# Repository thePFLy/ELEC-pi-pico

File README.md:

# ELEC-pi-pico
Développement d'une application télémètre à ultrasons qui envoie au pico la mesure d'une distance

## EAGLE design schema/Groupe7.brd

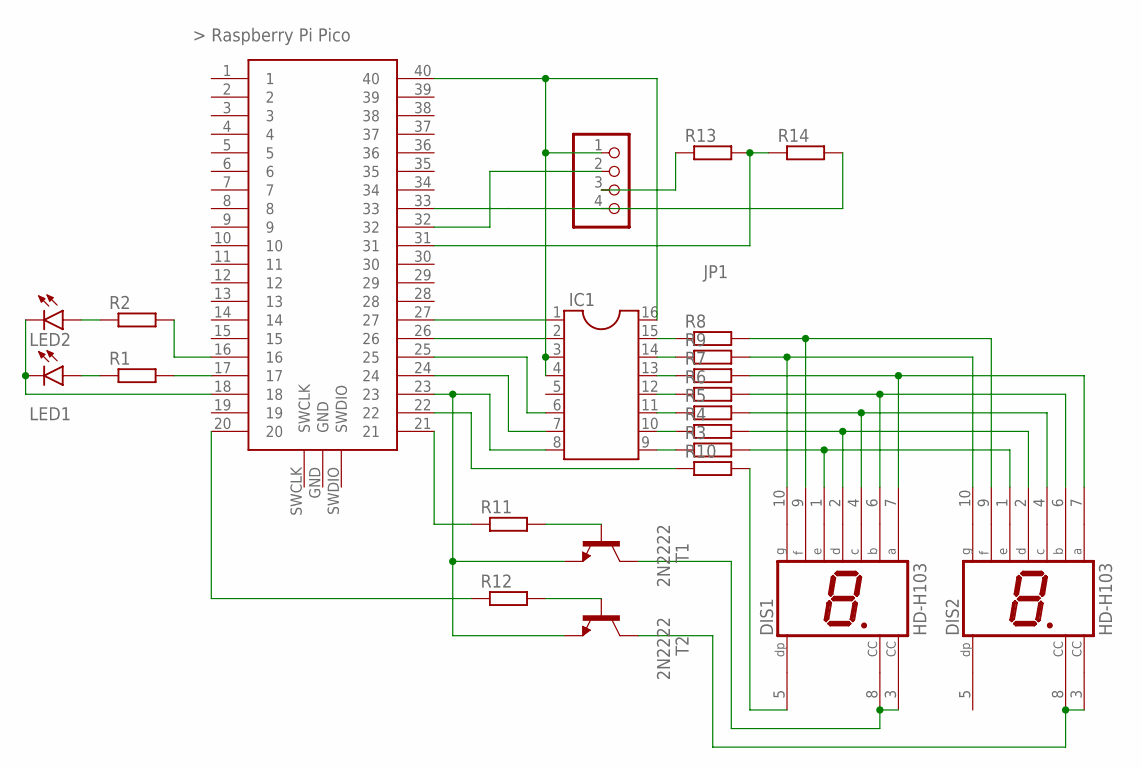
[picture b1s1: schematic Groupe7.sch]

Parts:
DIS1, DIS2: HD-H103; HDSP-M
IC1: DIL16
JP1: PINHD-1X4; 1X04
LED1, LED2: LED5MM
R1, R2, R3, R4, R5, R6, R7, R8, R9, R10, R11, R12, R13, R14: R-EU_0207/7; 0207/7
T1, T2: 2N2222; TO18
U$1: RASPBERRY-PI-PICO_TH; FT_RASPBERRY-PI-PICO_TH

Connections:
unnamed: IC1.15, R8.1
unnamed: IC1.14, R9.1
unnamed: IC1.13, R7.1
unnamed: IC1.12, R6.1
unnamed: IC1.11, R5.1
unnamed: IC1.10, R4.1
unnamed: IC1.9, R3.1
unnamed: IC1.1, U$1.27
unnamed: IC1.2, U$1.26
unnamed: IC1.6, U$1.25
unnamed: IC1.7, U$1.24
unnamed: DIS1.9 (F), DIS2.9 (F), R8.2
unnamed: DIS1.10 (G), DIS2.10 (G), R9.2
unnamed: DIS1.7 (A), DIS2.7 (A), R7.2
unnamed: DIS1.6 (B), DIS2.6 (B), R6.2
unnamed: DIS1.4 (C), DIS2.4 (C), R5.2
unnamed: DIS1.2 (D), DIS2.2 (D), R4.2
unnamed: DIS1.1 (E), DIS2.1 (E), R3.2
unnamed: IC1.3, IC1.4, IC1.16, JP1.1, U$1.40
unnamed: IC1.8, T1.1 (E), T2.1 (E), U$1.23
unnamed: JP1.2, U$1.32
unnamed: JP1.3, R13.1
unnamed: JP1.4, R14.2, U$1.33
unnamed: DIS1.3 (CC), DIS1.8 (CC), T1.3 (C)
unnamed: DIS2.3 (CC), DIS2.8 (CC), T2.3 (C)
unnamed: DIS1.5 (DP), R10.2
unnamed: R10.1, U$1.22
unnamed: R12.1, U$1.20
unnamed: R1.2, U$1.17
unnamed: R11.1, U$1.21
unnamed: R2.2, U$1.16
unnamed: LED2.A, R2.1
unnamed: LED1.A, R1.1
unnamed: LED1.K (C), LED2.K (C), U$1.18
unnamed: R11.2, T1.2 (B)
unnamed: R12.2, T2.2 (B)
unnamed: R13.2, R14.1, U$1.31

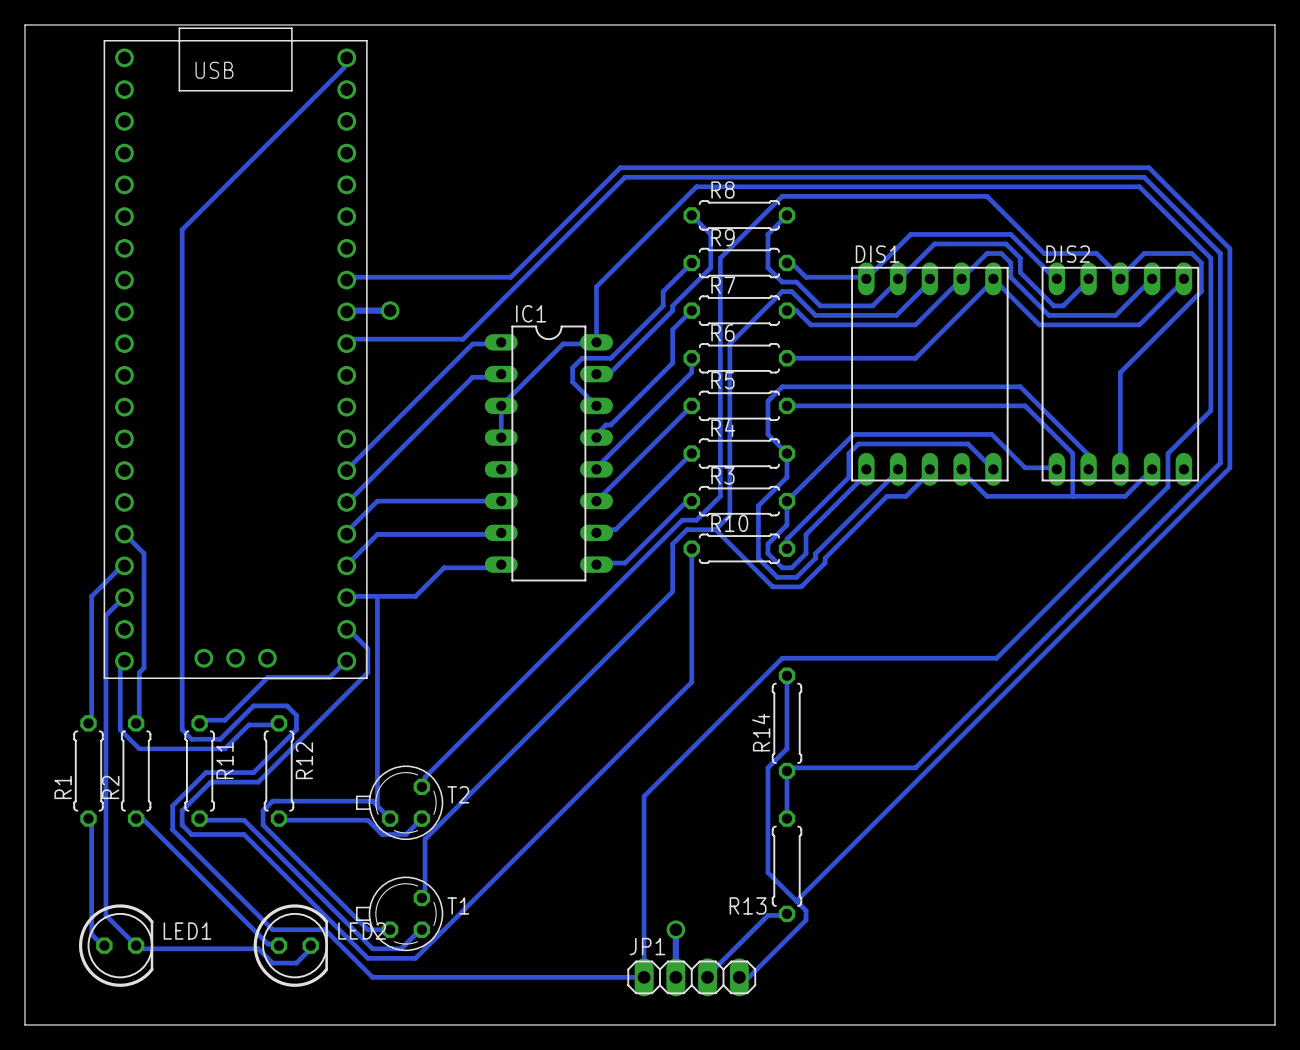
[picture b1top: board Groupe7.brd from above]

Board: 2 copper layers, 100.0 x 80.0 mm, 23 parts (0 on the bottom side), 37 nets.

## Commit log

2023-02-14 eagle and gui
    add eagle schema and customtkinter (not end)
2023-02-14 windows size
2023-02-27 remade pico code
2023-03-01 stuff
2023-03-04 working pcb
2023-03-04 temporary pcb
2023-03-12 Final brd
2023-03-15 final .brd
2023-04-26 should work now
2023-04-26 aled
2023-05-15 fixes
2023-05-16 more
2023-05-17 final
2023-05-17 poll marche pas
